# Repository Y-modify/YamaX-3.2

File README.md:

# YamaX 3.2

This is the software of humanoid robot named "YamaX 3.2"
The humanoid uses the original board with Intel Edison
This repository contains EAGLE files, 3D models, and Firmware.

Detailed information about this robot can be found in the following page: 

- [Y-modify](http://www.y-modify.org)
- [Y-modify Blog](http://blog.y-modify.org)

## Directory Structure

```
.
├── Designs
│   ├── model           #3D model
│   └── Axion 0.9	#EAGLE PCB file
├── Docs
│   └── LAYOUT.docx	#PCB Layout
└── Firmware	#Firmware (submodule of YamaX-Utils)
```

## Licence

These files are released under MIT Licence.
Please see `LICENCE`.

## Contact

You can comment on [our blog](http://blog.y-modify.org), or send e-mail to [info@y-modify.org](mailto:info@y-modify.org).

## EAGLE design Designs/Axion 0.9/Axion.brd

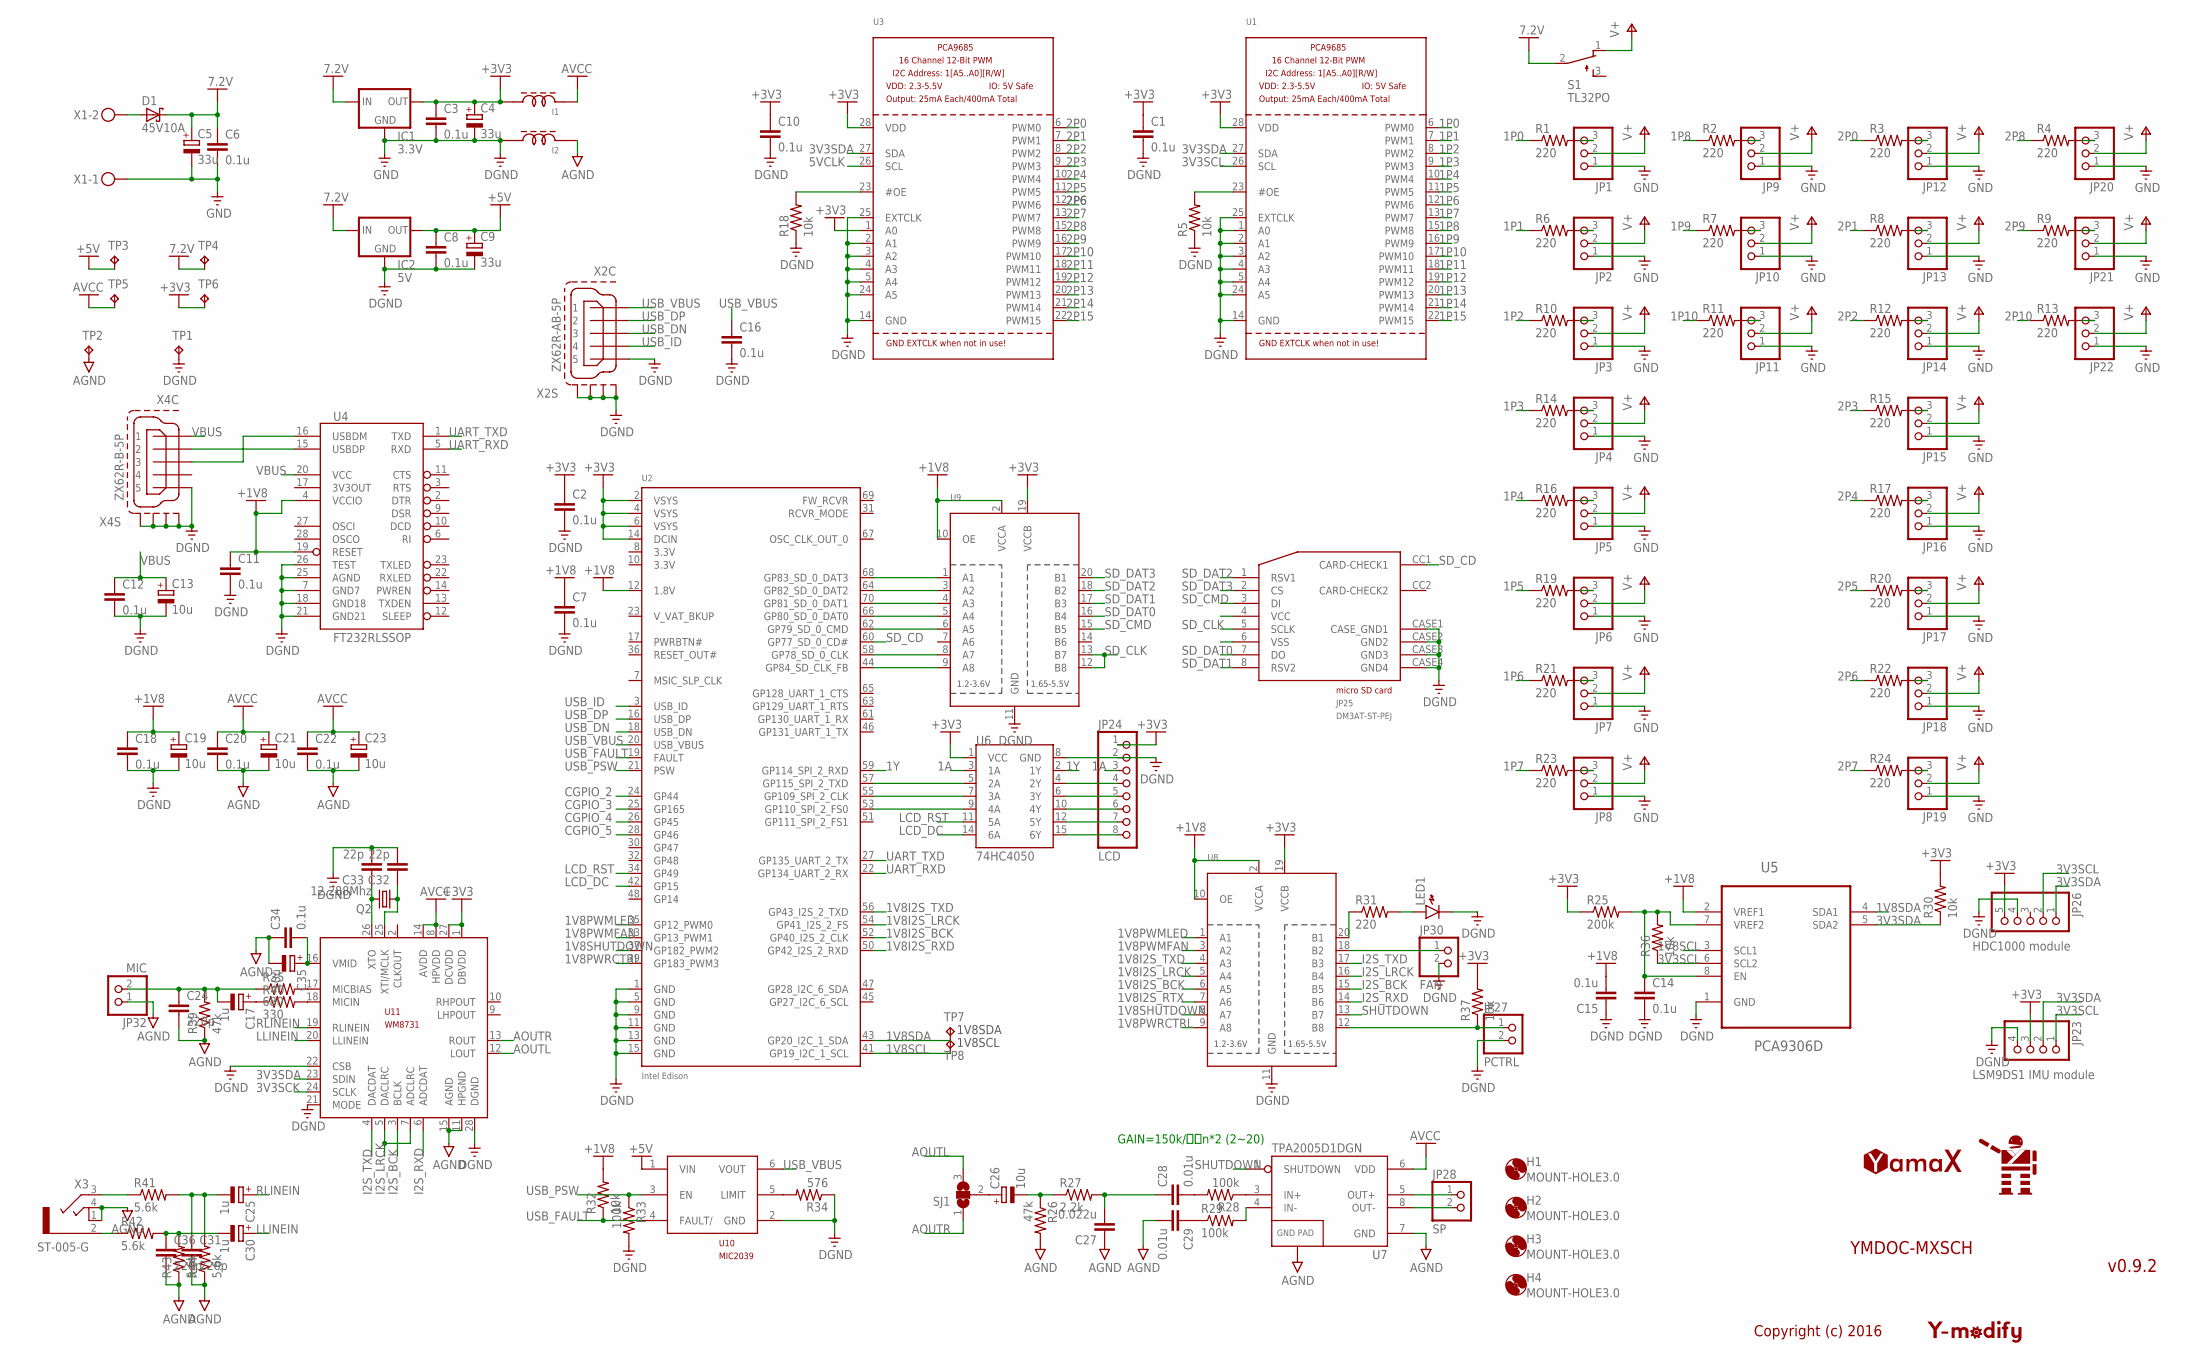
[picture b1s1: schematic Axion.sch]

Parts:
C1, C2, C3, C6, C7, C8, C10, C11, C12, C14, C15, C16, C18, C20, C22, C34: 0.1u; C1608
C4, C5, C9: 33u; E2-5
C13, C19, C21, C23, C26, C35: 10u; E2-5
C17, C25, C30: 1u; E2-5
C24, C31, C36: 220p; C0805
C27: 0.022u; C1608
C28, C29: 0.01u; C1608
C32, C33: 22p; C1608
D1: 45V10A; DO201T15
H1, H2, H3, H4: MOUNT-HOLE3.0; 3,0
I1, I2: BLM18; 1608(1.6*0.8MM)
IC1: 3.3V; 78XXS
IC2: 5V; 78XXS
JP1, JP2, JP3, JP4, JP5, JP6, JP7, JP8, JP9, JP10, JP11, JP12, JP13, JP14, JP15, JP16, JP17, JP18, JP19, JP20, JP21, JP22: PINHD-1X3; 1X03
JP23: LSM9DS1 IMU module; 1X04
JP24: LCD; 1X08
JP25: DM3AT-ST-PEJ; DM3AT-SF-PEJ
JP26: HDC1000 module; 1X05
JP27: PCTRL; 1X02
JP28: SP; 1X02
JP30: FAN; 1X02
JP32: MIC; 1X02
LED1: LED1608
Q2: 12.288Mhz; HC49/S
R1, R2, R3, R4, R6, R7, R8, R9, R10, R11, R12, R13, R14, R15, R16, R17, R19, R20, R21, R22, R23, R24, R31: 220; M1206
R5, R18, R30, R32, R36, R37: 10k; M1206
R25: 200k; 0309V
R26, R39: 47k; R0603
R27: 2.2k; R1206
R28, R29, R33: 100k; R0603
R34: 576; M1206
R35: 680; R1206
R40: 330; R1206
R41, R42, R43, R44: 5.6k; R1206
S1: TL32PO; TL3XPO
SJ1: SJ2W; SJ_2
TP1, TP2, TP3, TP4, TP5, TP6, TP7, TP8: TESTPAD-R-AUTO-0.5; ROUND-AUTO-0.5
U1, U3: PCA9685; TSSOP28
U2: Intel Edison; EDISON_DAUGHTER
U4: FT232RLSSOP; SSOP28DB
U5: PCA9306D; SOIC127P600X175-8N
U6: 74HC4050; SO016
U7: TPA2005D1DGN; POWER-SOP8
U8, U9: TXB0108PWR; TSSOP20
U10: MIC2039; SOT23-6
U11: WM8731; SSOP28
U$1: Y-MODIFY
U$2: YAMAX
U$4: MON
X1: MKDSN1,5/2-5,08
X2: ZX62R-AB-5P
X3: ST-005-G
X4: ZX62R-B-5P

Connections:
1A: JP24.3, U6.3 (1A)
1P0: R1.1, U1.6 (PWM0)
1P1: R6.1, U1.7 (PWM1)
1P2: R10.1, U1.8 (PWM2)
1P3: R14.1, U1.9 (PWM3)
1P4: R16.1, U1.10 (PWM4)
1P5: R19.1, U1.11 (PWM5)
1P6: R21.1, U1.12 (PWM6)
1P7: R23.1, U1.13 (PWM7)
1P8: R2.1, U1.15 (PWM8)
1P9: R7.1, U1.16 (PWM9)
1P10: R11.1, U1.17 (PWM10)
1P11: U1.18 (PWM11)
1P12: U1.19 (PWM12)
1P13: U1.20 (PWM13)
1P14: U1.21 (PWM14)
1P15: U1.22 (PWM15)
1V8I2S_BCK: U2.52 (GP40_I2S_2_CLK), U8.6 (A5)
1V8I2S_LRCK: U2.54 (GP41_I2S_2_FS), U8.5 (A4)
1V8I2S_RTX: U8.7 (A6)
1V8I2S_RXD: U2.50 (GP42_I2S_2_RXD)
1V8I2S_TXD: U2.56 (GP43_I2S_2_TXD), U8.4 (A3)
1V8PWMFAN: U2.33 (GP13_PWM1), U8.3 (A2)
1V8PWMLED: U2.35 (GP12_PWM0), U8.1 (A1)
1V8PWRCTRL: U2.39 (GP183_PWM3), U8.9 (A8)
1V8SCL: TP8.TP, U2.41 (GP19_I2C_1_SCL), U5.3 (SCL1)
1V8SDA: TP7.TP, U2.43 (GP20_I2C_1_SDA), U5.4 (SDA1)
1V8SHUTDOWN: U2.37 (GP182_PWM2), U8.8 (A7)
1Y: U2.59 (GP114_SPI_2_RXD), U6.2 (1Y)
2P0: R3.1, U3.6 (PWM0)
2P1: R8.1, U3.7 (PWM1)
2P2: R12.1, U3.8 (PWM2)
2P3: R15.1, U3.9 (PWM3)
2P4: R17.1, U3.10 (PWM4)
2P5: R20.1, U3.11 (PWM5)
2P6: R22.1, U3.12 (PWM6)
2P7: R24.1, U3.13 (PWM7)
2P8: R4.1, U3.15 (PWM8)
2P9: R9.1, U3.16 (PWM9)
2P10: R13.1, U3.17 (PWM10)
2P11: U3.18 (PWM11)
2P12: U3.19 (PWM12)
2P13: U3.20 (PWM13)
2P14: U3.21 (PWM14)
2P15: U3.22 (PWM15)
3V3SCK: U11.24 (SCLK)
3V3SCL: JP23.1, JP26.2, R36.1, U1.26 (SCL), U5.6 (SCL2)
3V3SDA: JP23.2, JP26.1, R30.1, U1.27 (SDA), U3.27 (SDA), U5.5 (SDA2), U11.23 (SDIN)
5VCLK: U3.26 (SCL)
+1V8: C7.1, C11.1, C15.2, C18.1, C19.+, R32.2, U2.12 (1.8V), U4.4 (VCCIO), U4.19 (RESET), U5.2 (VREF1), U8.2 (VCCA), U8.10 (OE), U9.2 (VCCA), U9.10 (OE)
+3V3: C1.1, C2.1, C3.1, C4.+, C10.1, I1.P$3, IC1.OUT, JP23.3, JP24.1, JP26.5, R25.1, R30.2, R37.2, TP6.TP, U1.28 (VDD), U2.2 (VSYS), U2.4 (VSYS), U2.6 (VSYS), U2.14 (DCIN), U3.1 (A0), U3.28 (VDD), U6.1 (VCC), U8.19 (VCCB), U9.19 (VCCB), U11.1 (DBVDD), U11.27 (DCVDD)
+5V: C8.1, C9.+, IC2.OUT, TP3.TP, U10.1 (VIN)
AGND: C20.2, C21.-, C22.2, C23.-, C24.2, C27.1, C29.2, C31.2, C34.1, C35.-, C36.2, I2.P$4, JP32.1, R26.2, R39.1, R43.1, R44.1, TP2.TP, U7.7 (GND), U7.9 (GND), U11.11 (HPGND), U11.15 (AGND), X3.1 (3), X3.4 (2)
AOUTL: SJ1.3, U11.12 (LOUT)
AOUTR: SJ1.1, U11.13 (ROUT)
AVCC: C20.1, C21.+, C22.1, C23.+, I1.P$4, TP5.TP, U7.6 (VDD), U11.8 (HPVDD), U11.14 (AVDD)
CGPIO_2: U2.24 (GP44)
CGPIO_3: U2.25 (GP165)
CGPIO_4: U2.26 (GP45)
CGPIO_5: U2.28 (GP46)
DGND: C1.2, C2.2, C7.2, C8.2, C9.-, C10.2, C11.2, C12.2, C13.-, C14.2, C15.1, C16.2, C18.2, C19.-, C32.2, C33.2, IC2.GND, JP23.4, JP24.2, JP25.CASE1 (CASE_GND1), JP25.CASE2 (GND2), JP25.CASE3 (GND3), JP25.CASE4 (GND4), JP26.4, JP27.2, JP30.2, LED1.K, R5.1, R18.1, R33.2, R34.1, TP1.TP, U1.1 (A0), U1.2 (A1), U1.3 (A2), U1.4 (A3), U1.5 (A4), U1.14 (GND), U1.24 (A5), U1.25 (EXTCLK), U2.1 (GND), U2.5 (GND), U2.9 (GND), U2.11 (GND), U2.13 (GND), U2.15 (GND), U3.2 (A1), U3.3 (A2), U3.4 (A3), U3.5 (A4), U3.14 (GND), U3.24 (A5), U3.25 (EXTCLK), U4.7 (GND7), U4.18 (GND18), U4.21 (GND21), U4.25 (AGND), U4.26 (TEST), U5.1 (GND), U6.8 (GND), U8.11 (GND), U9.11 (GND), U10.2 (GND), U11.21 (MODE), U11.22 (CSB), U11.28 (DGND), X2.5, X2.S1, X2.S2, X2.S3, X2.S4, X4.5, X4.S1, X4.S2, X4.S3, X4.S4
GND: C3.2, C4.-, C5.-, C6.2, I2.P$3, IC1.GND, JP1.1, JP2.1, JP3.1, JP4.1, JP5.1, JP6.1, JP7.1, JP8.1, JP9.1, JP10.1, JP11.1, JP12.1, JP13.1, JP14.1, JP15.1, JP16.1, JP17.1, JP18.1, JP19.1, JP20.1, JP21.1, JP22.1, X1.1
I2S_BCK: U8.15 (B5), U11.3 (BCLK)
I2S_LRCK: U8.16 (B4), U11.5 (DACLRC), U11.7 (ADCLRC)
I2S_RXD: U8.14 (B6), U11.6 (ADCDAT)
I2S_TXD: U8.17 (B3), U11.4 (DACDAT)
LCD_DC: U2.42 (GP15), U6.14 (6A)
LCD_RST: U2.34 (GP49), U6.11 (5A)
LLINEIN: C30.+, U11.20 (LLINEIN)
unnamed: JP1.3, R1.2
unnamed: D1.A, X1.2
unnamed: JP2.3, R6.2
unnamed: R5.2, U1.23 (#OE)
unnamed: JP3.3, R10.2
unnamed: R18.2, U3.23 (#OE)
unnamed: JP4.3, R14.2
unnamed: U4.15 (USBDP), U4.16 (USBDM), X4.2, X4.3
unnamed: JP5.3, R16.2
unnamed: C14.1, R25.2, R36.2, U5.7 (VREF2), U5.8 (EN)
unnamed: JP6.3, R19.2
unnamed: U2.53 (GP110_SPI_2_FS0), U6.9 (4A)
unnamed: JP7.3, R21.2
unnamed: U2.55 (GP109_SPI_2_CLK), U6.7 (3A)
unnamed: JP8.3, R23.2
unnamed: JP24.8, U6.15 (6Y)
unnamed: JP9.3, R2.2
unnamed: JP10.3, R7.2
unnamed: JP11.3, R11.2
unnamed: JP20.3, R4.2
unnamed: JP21.3, R9.2
unnamed: JP22.3, R13.2
unnamed: JP24.7, U6.12 (5Y)
unnamed: JP24.6, U6.10 (4Y)
unnamed: JP24.5, U6.6 (3Y)
unnamed: JP12.3, R3.2
unnamed: JP13.3, R8.2
unnamed: JP14.3, R12.2
unnamed: JP15.3, R15.2
unnamed: JP16.3, R17.2
unnamed: JP17.3, R20.2
unnamed: JP18.3, R22.2
unnamed: JP19.3, R24.2
unnamed: JP24.4, U6.4 (2Y)
unnamed: JP27.1, R37.1, U8.12 (B8)
unnamed: U2.68 (GP83_SD_0_DAT3), U9.1 (A1)
unnamed: C17.+, R40.1
unnamed: U2.57 (GP115_SPI_2_TXD), U6.5 (2A)
unnamed: U2.64 (GP82_SD_0_DAT2), U9.3 (A2)
unnamed: U2.70 (GP81_SD_0_DAT1), U9.4 (A3)
unnamed: U2.66 (GP80_SD_0_DAT0), U9.5 (A4)
unnamed: U2.62 (GP79_SD_0_CMD), U9.6 (A5)
unnamed: U2.58 (GP78_SD_0_CLK), U9.8 (A7)
unnamed: U2.44 (GP84_SD_CLK_FB), U9.9 (A8)
unnamed: C26.+, SJ1.2
unnamed: C26.-, R26.1, R27.1
unnamed: R28.1, U7.3 (IN+)
unnamed: R29.2, U7.4 (IN-)
unnamed: C28.2, R28.2
unnamed: C29.1, R29.1
unnamed: C27.2, C28.1, R27.2
unnamed: JP28.1, U7.5 (OUT+)
unnamed: JP28.2, U7.8 (OUT-)
unnamed: R41.1, X3.3 (1)
unnamed: R42.1, X3.2 (4)
unnamed: C30.-, C36.1, R42.2, R43.2
unnamed: C25.-, C31.1, R41.2, R44.2
unnamed: R31.1, U8.20 (B1)
unnamed: LED1.A, R31.2
unnamed: JP30.1, U8.18 (B2)
unnamed: C33.1, Q2.2, U11.26 (XTO)
unnamed: R34.2, U10.5 (LIMIT)
unnamed: C32.1, Q2.1, U11.25 (XTI/MCLK)
unnamed: C34.2, C35.+, U11.16 (VMID)
unnamed: R35.2, U11.17 (MICBIAS)
unnamed: R40.2, U11.18 (MICIN)
unnamed: C17.-, C24.1, JP32.2, R35.1, R39.2
RLINEIN: C25.+, U11.19 (RLINEIN)
SD_CD: JP25.CC1 (CARD-CHECK1), U2.60 (GP77_SD_0_CD#)
SD_CLK: JP25.5 (SCLK), U9.12 (B8), U9.13 (B7)
SD_CMD: JP25.3 (DI), U9.15 (B5)
SD_DAT0: JP25.7 (DO), U9.16 (B4)
SD_DAT1: JP25.8 (RSV2), U9.17 (B3)
SD_DAT2: JP25.1 (RSV1), U9.18 (B2)
SD_DAT3: JP25.2 (CS), U9.20 (B1)
SHUTDOWN: U7.1 (SHUTDOWN), U8.13 (B7)
UART_RXD: U2.22 (GP134_UART_2_RX), U4.5 (RXD)
UART_TXD: U2.27 (GP135_UART_2_TX), U4.1 (TXD)
USB_DN: U2.18 (USB_DN), X2.3
USB_DP: U2.16 (USB_DP), X2.2
USB_FAULT: R32.1, U2.19 (FAULT), U10.4 (FAULT/)
USB_ID: U2.3 (USB_ID), X2.4
USB_PSW: R33.1, U2.21 (PSW), U10.3 (EN)
USB_VBUS: C16.1, U2.20 (USB_VBUS), U10.6 (VOUT), X2.1
V+: JP1.2, JP2.2, JP3.2, JP4.2, JP5.2, JP6.2, JP7.2, JP8.2, JP9.2, JP10.2, JP11.2, JP12.2, JP13.2, JP14.2, JP15.2, JP16.2, JP17.2, JP18.2, JP19.2, JP20.2, JP21.2, JP22.2, S1.1 (O)
VBUS: C12.1, C13.+, U4.20 (VCC), X4.1
VCC: C5.+, C6.1, D1.C, IC1.IN, IC2.IN, S1.2, TP4.TP

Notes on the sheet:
Copyright (c) 2016
v0.9.2
YMDOC-MXSCH
GAIN=150k/Ｒｉn*2 (2~20)

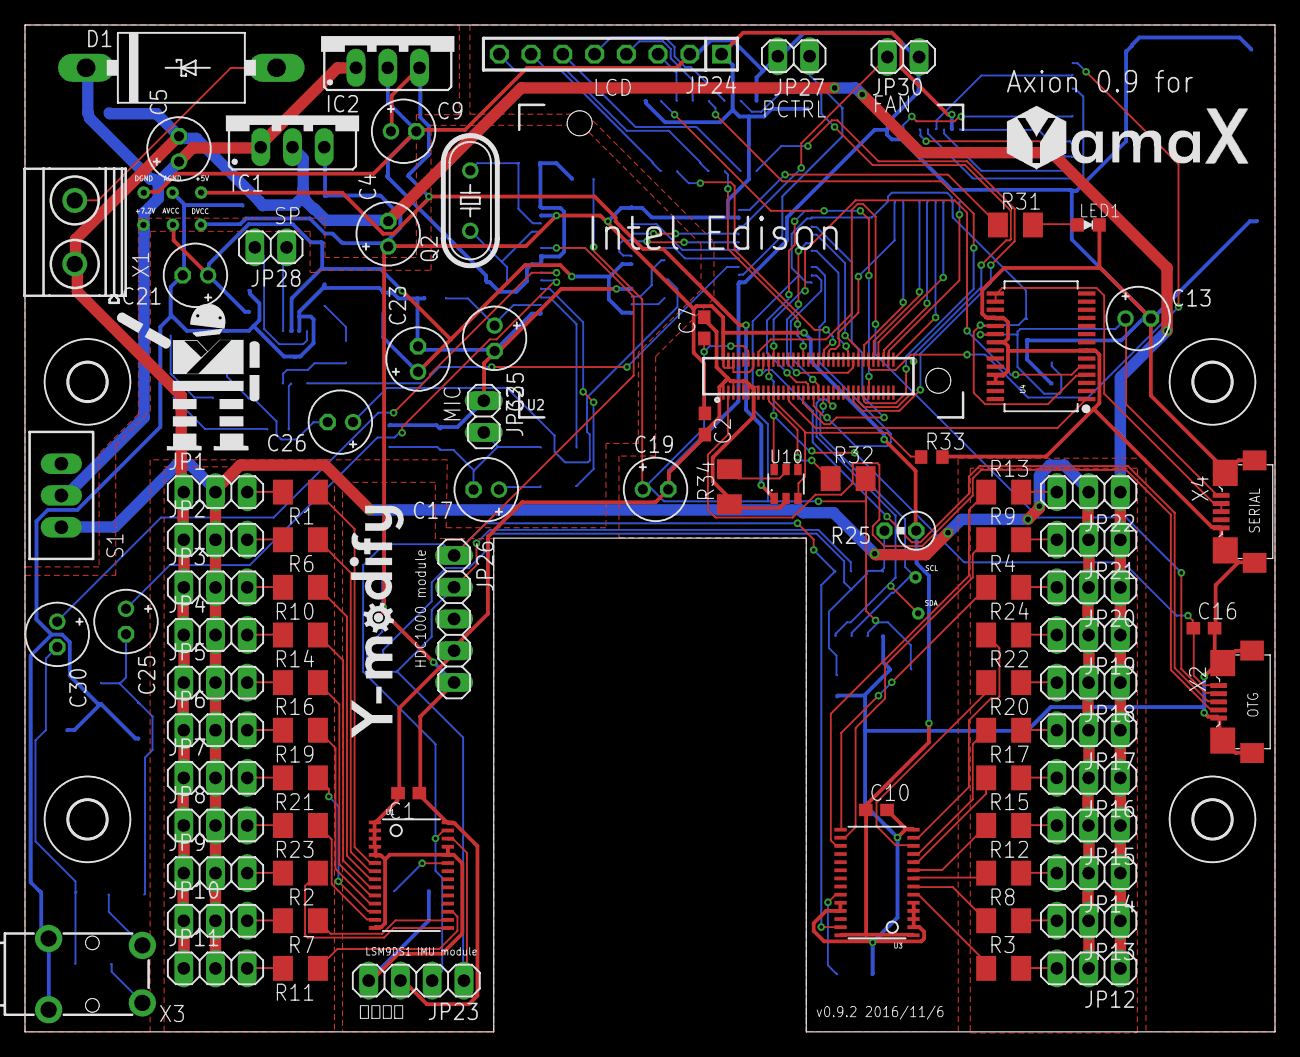
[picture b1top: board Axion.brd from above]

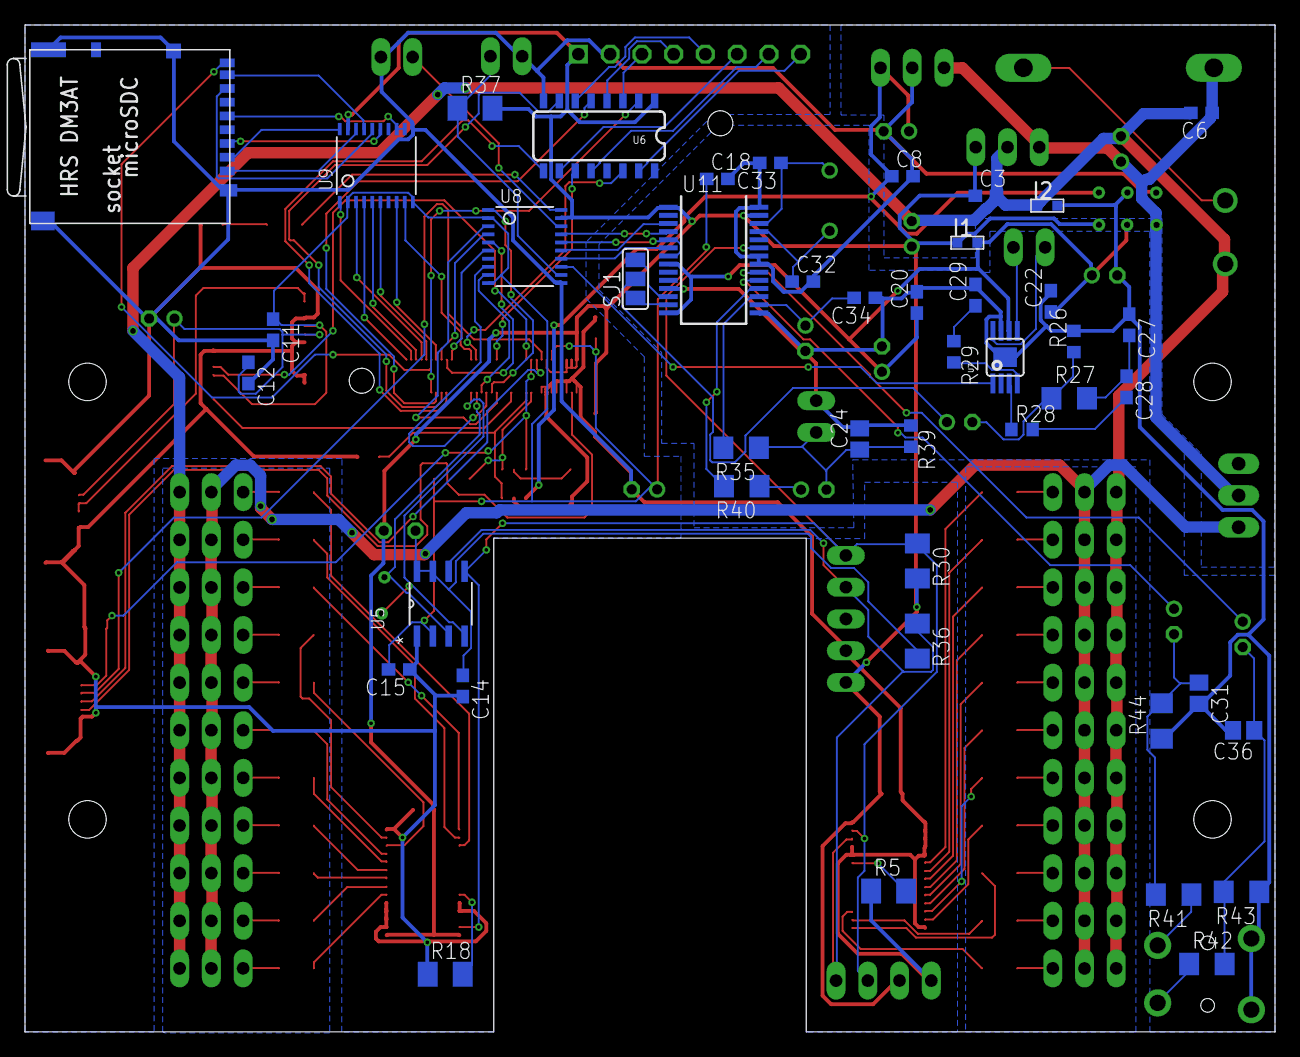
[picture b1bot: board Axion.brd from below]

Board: 2 copper layers, 100.0 x 80.5 mm, 148 parts (45 on the bottom side), 138 nets.

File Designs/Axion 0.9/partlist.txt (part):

Partlist

Exported from Axion.sch at 2016/11/06 23:59

EAGLE Version 7.7.0 Copyright (c) 1988-2016 CadSoft

Assembly variant: 

Part     Value              Device                              Package            Library                  Sheet

C1       0.1u               C-EUC1608                           C1608              resistor                 1
C2       0.1u               C-EUC1608                           C1608              resistor                 1
C3       0.1u               C-EUC1608                           C1608              resistor                 1
C4       33u                CPOL-EUE2-5                         E2-5               resistor                 1
C5       33u                CPOL-EUE2-5                         E2-5               resistor                 1
C6       0.1u               C-EUC1608                           C1608              resistor                 1
C7       0.1u               C-EUC1608                           C1608              resistor                 1
C8       0.1u               C-EUC1608                           C1608              resistor                 1
C9       33u                CPOL-EUE2-5                         E2-5               resistor                 1
C10      0.1u               C-EUC1608                           C1608              resistor                 1
C11      0.1u               C-EUC1608                           C1608              resistor                 1
C12      0.1u               C-EUC1608                           C1608              resistor                 1
C13      10u                CPOL-EUE2-5                         E2-5               resistor                 1
C14      0.1u               C-EUC1608                           C1608              resistor                 1
C15      0.1u               C-EUC1608                           C1608              resistor                 1
C16      0.1u               C-EUC1608                           C1608              resistor                 1
C17      1u                 CPOL-EUE2-5                         E2-5               resistor                 1
C18      0.1u               C-EUC1608                           C1608              resistor                 1
C19      10u                CPOL-EUE2-5                         E2-5               resistor                 1
C20      0.1u               C-EUC1608                           C1608              resistor                 1
C21      10u                CPOL-EUE2-5                         E2-5               resistor                 1
C22      0.1u               C-EUC1608                           C1608              resistor                 1
C23      10u                CPOL-EUE2-5                         E2-5               resistor                 1
C24      220p               C-EUC0805                           C0805              resistor                 1
C25      1u                 CPOL-EUE2-5                         E2-5               resistor                 1
C26      10u                CPOL-EUE2-5                         E2-5               resistor                 1
C27      0.022u             C-EUC1608                           C1608              resistor                 1
C28      0.01u              C-EUC1608                           C1608              resistor                 1
C29      0.01u              C-EUC1608                           C1608              resistor                 1
C30      1u                 CPOL-EUE2-5                         E2-5               resistor                 1
C31      220p               C-EUC0805                           C0805              resistor                 1
C32      22p                C-EUC1608                           C1608              resistor                 1
C33      22p                C-EUC1608                           C1608              resistor                 1
C34      0.1u               C-EUC1608                           C1608              resistor                 1
C35      10u                CPOL-EUE2-5                         E2-5               resistor                 1
C36      220p               C-EUC0805                           C0805              resistor                 1
D1       45V10A             SCHOTTKY-DIODEDO201T15              DO201T15           diode-1                  1
I1                          BLM18                               1608(1.6*0.8MM)    Inductor                 1
I2                          BLM18                               1608(1.6*0.8MM)    Inductor                 1
IC1      3.3V               78XXS                               78XXS              v-reg                    1
IC2      5V                 78XXS                               78XXS              v-reg                    1
JP1                         PINHD-1X3                           1X03               pinhead                  1
JP2                         PINHD-1X3                           1X03               pinhead                  1
JP3                         PINHD-1X3                           1X03               pinhead                  1
JP4                         PINHD-1X3                           1X03               pinhead                  1
JP5                         PINHD-1X3                           1X03               pinhead                  1
JP6                         PINHD-1X3                           1X03               pinhead                  1
JP7                         PINHD-1X3                           1X03               pinhead                  1
JP8                         PINHD-1X3                           1X03               pinhead                  1
JP9                         PINHD-1X3                           1X03               pinhead                  1
JP10                        PINHD-1X3                           1X03               pinhead                  1
JP11                        PINHD-1X3                           1X03               pinhead                  1
JP12                        PINHD-1X3                           1X03               pinhead                  1
JP13                        PINHD-1X3                           1X03               pinhead                  1
JP14                        PINHD-1X3                           1X03               pinhead                  1
JP15                        PINHD-1X3                           1X03               pinhead                  1
JP16                        PINHD-1X3                           1X03               pinhead                  1
JP17                        PINHD-1X3                           1X03               pinhead                  1
JP18                        PINHD-1X3                           1X03               pinhead                  1
JP19                        PINHD-1X3                           1X03               pinhead                  1
JP20                        PINHD-1X3                           1X03               pinhead                  1
JP21                        PINHD-1X3                           1X03               pinhead                  1
JP22                        PINHD-1X3                           1X03               pinhead                  1
JP23     LSM9DS1 IMU module PINHD-1X4                           1X04               pinhead                  1
JP24     LCD                PINHD-1X8                           1X08               pinhead                  1
JP25     DM3AT-ST-PEJ       DM3AT-ST-PEJ                        DM3AT-SF-PEJ       SD Card Socket           1
JP26     HDC1000 module     PINHD-1X5                           1X05               pinhead                  1
JP27     PCTRL              PINHD-1X2                           1X02               pinhead                  1
JP28     SP                 PINHD-1X2                           1X02               pinhead                  1
JP30     FAN                PINHD-1X2                           1X02               pinhead                  1
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
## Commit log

2016-11-07 Initial Commit. Added EAGLE PCB files.
2016-11-07 Modified README Added LICENSE
2017-04-01 Added 3D models Added firmware

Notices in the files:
parts and their libraries:
SparkFun-Boards: Licensing: Creative Commons ShareAlike 4.0 International - https://creativecommons.org/licenses/by-sa/4.0
supply0: Copyright (C) 2007, Bob Starr
